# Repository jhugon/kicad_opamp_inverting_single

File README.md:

# Single Inverting Opamp Board in KiCAD

This is meant to be a general inverting opamp board for single, standard SOIC8
op-amps.

This is a 4-layer board with (mostly) 0805 components, sinking and sourcing
from SMA connectors.

Example parts:

- THS4011
- LMH6654
- OPA657
- ADA4895-1
- LTC6228

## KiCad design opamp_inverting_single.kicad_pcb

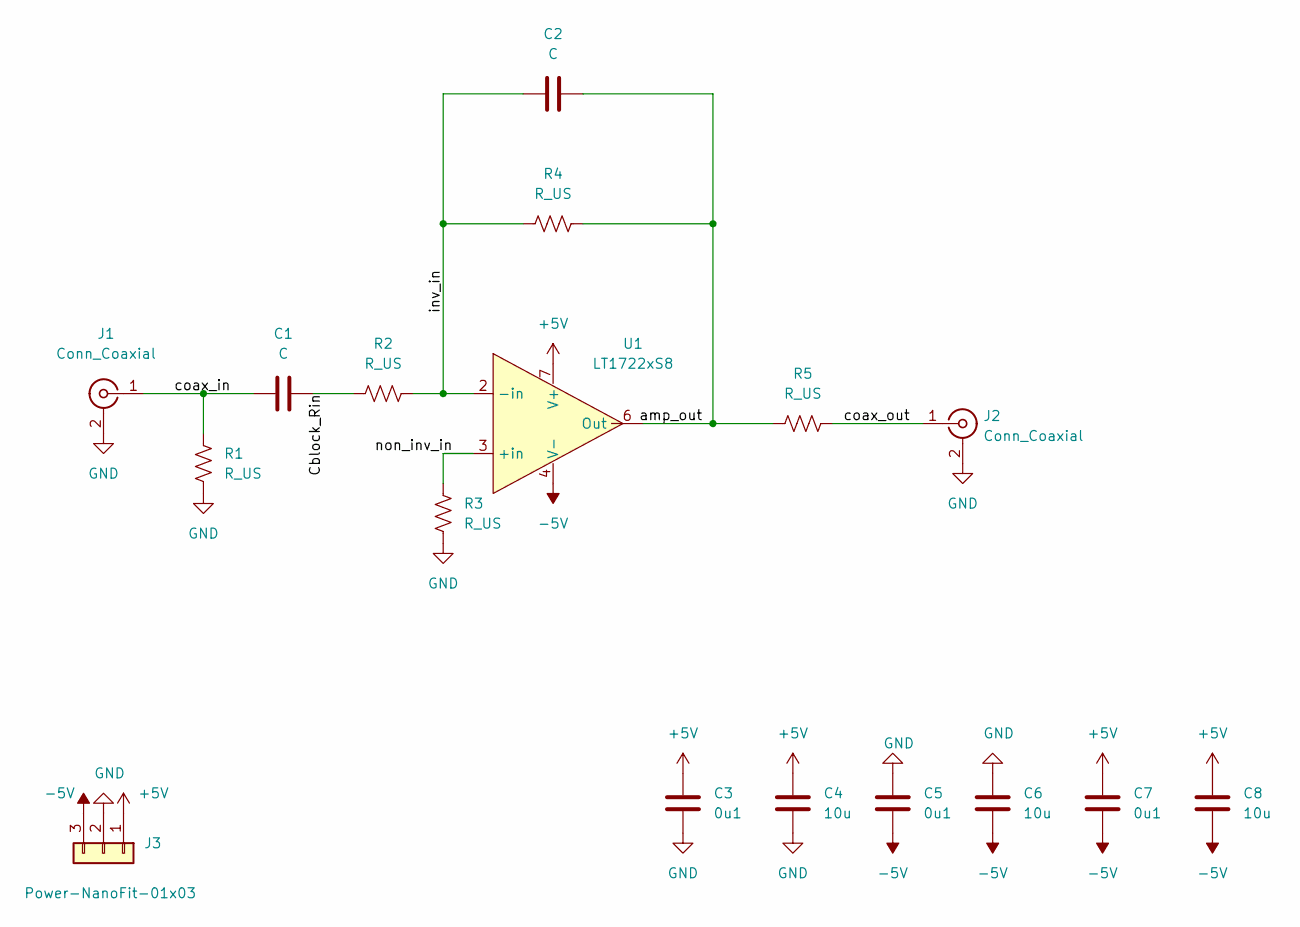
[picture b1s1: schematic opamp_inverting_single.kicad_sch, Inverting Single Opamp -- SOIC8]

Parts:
C1, C2: C; C_0805_2012Metric_Pad1.18x1.45mm_HandSolder
C3, C5, C7: 0u1; C_0805_2012Metric_Pad1.18x1.45mm_HandSolder
C4, C6, C8: 10u; C_0805_2012Metric_Pad1.18x1.45mm_HandSolder
J1, J2: Conn_Coaxial; SMA_Amphenol_132289_EdgeMount
J3: Power-NanoFit-01x03; Molex_Nano-Fit_105313-xx03_1x03_P2.50mm_Horizontal
R1, R2, R3, R4, R5: R_US; R_0805_2012Metric_Pad1.20x1.40mm_HandSolder
U1: LT1722xS8; SOIC-8_3.9x4.9mm_P1.27mm

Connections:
+5V: C3.2, C4.2, C7.2, C8.2, J3.1, U1.7 (V+)
-5V: C5.1, C6.1, C7.1, C8.1, J3.3, U1.4 (V-)
/Cblock_Rin: C1.2, R2.1
/amp_out: C2.2, R4.2, R5.1, U1.6 (Out)
/coax_in: C1.1, J1.1 (In), R1.2
/coax_out: J2.1 (In), R5.2
/inv_in: C2.1, R2.2, R4.1, U1.2 (-in)
/non_inv_in: R3.1, U1.3 (+in)
GND: C3.1, C4.1, C5.2, C6.2, J1.2 (Ext), J2.2 (Ext), J3.2, R1.1, R3.2

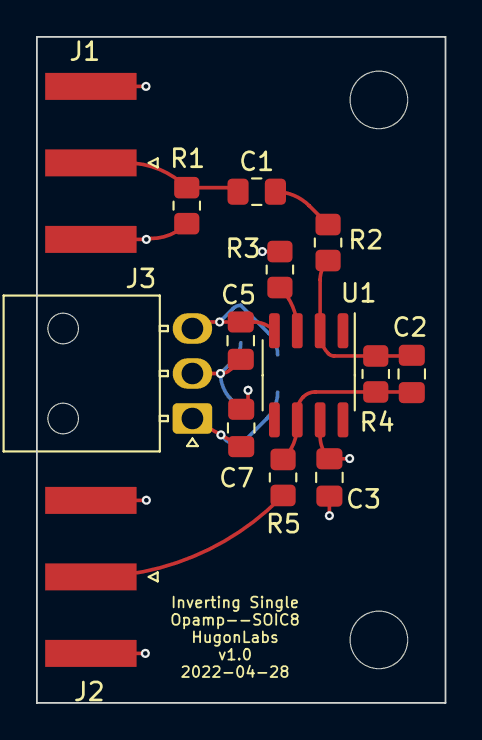
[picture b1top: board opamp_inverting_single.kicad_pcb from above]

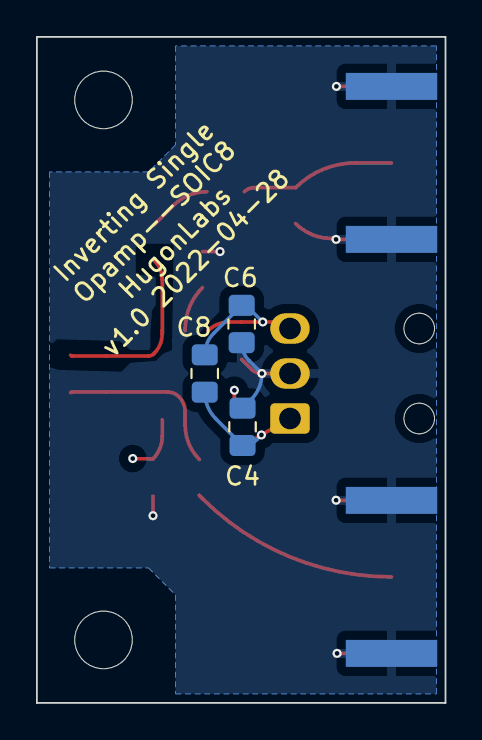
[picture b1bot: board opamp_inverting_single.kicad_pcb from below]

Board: 4 copper layers, 22.7 x 37.0 mm, 17 parts (3 on the bottom side), 9 nets.

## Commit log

2022-04-28 Added KiCAD project files and set up schem and pcb
2022-04-28 Added libraries to project
2022-04-28 finished schematic and rough pcb layout
    updated libraries to get power nanofit
2022-04-28 some routing
2022-04-28 Completed PCB
2022-04-28 Gerbers as submitted to fab for V1.0
2022-05-15 added extra ex. parts to README
